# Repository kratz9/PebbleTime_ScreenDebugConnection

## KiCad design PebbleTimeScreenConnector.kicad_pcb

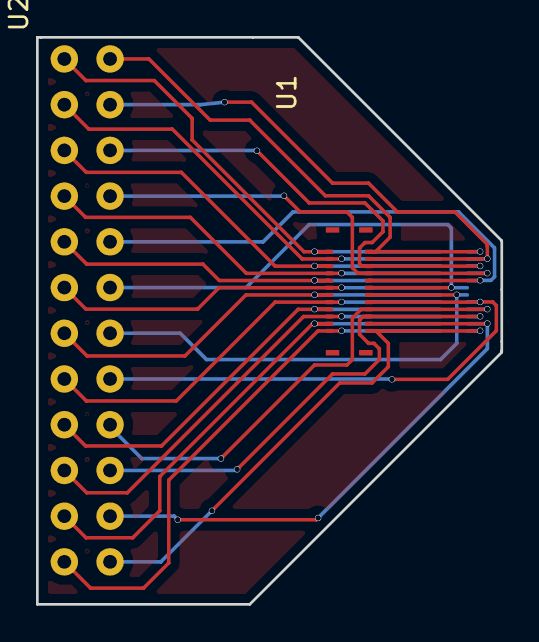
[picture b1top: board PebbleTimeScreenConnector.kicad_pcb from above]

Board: 2 copper layers, 25.8 x 31.5 mm, 3 parts (1 on the bottom side), 24 nets.

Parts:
U1: RECPT_24POS_SMD; CONN_RCPT_24POS_0.4MM_SMD
U2: 24_PIN_HDR_TH; 24_PIN_2ROW_HEADER
U3: RECPT_24POS_SMD; CONN_HDR_24POS_0.4MM_SMD

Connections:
unnamed: U1.1, U2.1, U3.1
unnamed: U1.2, U2.2, U3.2
unnamed: U1.3, U2.3, U3.3
unnamed: U1.4, U2.4, U3.4
unnamed: U1.5, U2.5, U3.5
unnamed: U1.6, U2.6, U3.6
unnamed: U1.7, U2.7, U3.7
unnamed: U1.8, U2.8, U3.8
unnamed: U1.9, U2.9, U3.9
unnamed: U1.10, U2.10, U3.10
unnamed: U1.11, U2.11, U3.11
unnamed: U1.12, U2.12, U3.12
unnamed: U1.13, U2.13, U3.13
unnamed: U1.14, U2.14, U3.14
unnamed: U1.15, U2.15, U3.15
unnamed: U1.16, U2.16, U3.16
unnamed: U1.17, U2.17, U3.17
unnamed: U1.18, U2.18, U3.18
unnamed: U1.19, U2.19, U3.19
unnamed: U1.20, U2.20, U3.20
unnamed: U1.21, U2.21, U3.21
unnamed: U1.22, U2.22, U3.22
unnamed: U1.23, U2.23, U3.23
unnamed: U1.24, U2.24, U3.24

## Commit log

2017-12-07 :space_invader: Added .gitattributes & .gitignore files
2017-12-07 1
    1
